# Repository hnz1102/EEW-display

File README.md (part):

<div align="center">
  <h1><code>EEW Display</code></h1>
</div>

ESP32-S3 firmware for a small earthquake-information display.  It shows recent
earthquakes and emergency earthquake warnings (緊急地震速報, EEW) from
[P2P地震情報](https://www.p2pquake.net/), draws the epicenters on a Google map,
and serves the same data (plus configuration) over Wi-Fi to a browser.  The
display is a 480×320 ILI9488 SPI TFT in landscape orientation; a MAX98357A
amplifier with an on-board speaker speaks EEWs and new earthquakes in Japanese.
Written in Rust (esp-idf-hal / esp-idf-svc).  The KiCad design of the board is in
[`hw/`](hw/) and a 3D-printable enclosure in [`STL/`](STL/) (see
[Hardware](#hardware)).

## Features

| Feature | Description |
|---------|-------------|
| Earthquake list | The 20 most recent events (8 rows visible, the list scrolls with the highlight): time (JST), magnitude, maximum intensity, depth, epicenter coordinates and tsunami flag |
| Map | Google Maps Static API tile (satellite or roadmap) filling the screen, with the recent epicenters drawn on it, sized by magnitude and coloured by intensity; Japan overview by default, or centred on the quake picked in the list.  The nearest well-known place, with distance and direction, is shown for the selected / new / EEW epicenter |
| EEW alert | On a warning the TFT switches to the map by itself, marks the forecast epicenter with a red `X` and shows magnitude, maximum forecast intensity and depth; the Web UI shows a red banner |
| 震度速報 | The JMA seismic-intensity flash (issued about 1.5 minutes after a quake of intensity 3 or more, before the epicenter is known) is announced and shown at once — maximum intensity and the areas that observed it — and replaced by the full report when that arrives |
| Voice | Chime + Japanese spoken announcement of every EEW, 震度速報 and newly received earthquake through the on-board MAX98357A amplifier and speaker; each can be switched off, and the volume set, in the Web UI (see [Spoken announcements](#spoken-announcements-japanese)) |
| Screen saver / idle clock | After a configurable idle time the backlight goes off, or a full-screen analog clock (JST) is shown; a button press or an EEW / new earthquake returns to the pages (see [Screen saver and idle clock](#screen-saver-and-idle-clock)) |
| Time sync | NTP (up to 4 servers) |
| Web UI | Browser-based configuration, earthquake list, map, audio controls |
| WPS | Wi-Fi Protected Setup (PBC mode), started at boot when no SSID is set |
| Syslog | Optional UDP syslog (RFC 5424) |
| Self-monitoring | Thread heartbeats and a software watchdog that restarts the unit when the feed or audio thread stalls or the WebSocket stays down; a `[DIAG]` status line every 10 minutes (see [Health monitoring](#health-monitoring)) |

---

## Hardware

The unit is a single 2-layer PCB, **EEW DISPLAY Rev.2** (139 × 64 mm), with the
3.5" TFT module plugged onto it, in a 3D-printed enclosure.

| Part | On the board |
|------|--------------|
| MCU | ESP32-S3-WROOM-1-N16R8 (16 MB flash, 8 MB octal PSRAM) |
| Display | **ILI9488 480×320** SPI TFT module (4-wire SPI, 18-bit colour), landscape.  The module's touch controller and SD-card slot are wired to the ESP32 but not used by the firmware |
| USB | USB-C (USB4105-GF-A): power, charging, and flashing / serial log through the ESP32-S3's native USB (5.1 kΩ CC pull-downs) |
| Battery | LiPo on a JST PH 2-pin connector, charged by an MCP73831 (500 mA); red LED = charging, green = charged.  A P-MOSFET power path runs the unit from USB when plugged in.  The supply voltage is read on GPIO11 through a 20 k / 20 k divider (see `adc_conversion_factor`) |
| Power switch | Slide switch (IS-1235-G) in front of the regulator |
| Regulator | SPX3819 LDO, 3.3 V |
| RTC | 32.768 kHz crystal on GPIO15/16 (the firmware falls back to the internal oscillator if absent) |
| Audio | MAX98357A I2S amplifier (48 kHz, 16-bit; SD_MODE high = on) driving an on-board speaker (UM1515IA).  The gain is set by the R12 / R13 option.  See [Spoken announcements](#spoken-announcements-japanese) |
| Buttons | Four 6 mm tactile switches: PAGE/BOOT (GPIO0), ZOOM-IN (GPIO38), ZOOM-OUT (GPIO39), MODE (GPIO40) |

### Board files ([`hw/`](hw/))

| File | Content |
|------|---------|
| [`schematic.pdf`](hw/schematic.pdf) | Schematic |
| `EEW-display.kicad_sch` / `.kicad_pcb` / `.kicad_pro` | KiCad project |
| `Library.pretty/` | Project footprints (ESP32-S3 module, TFT module, USB-C, slide switch, speaker, MAX98357A TQFN) |
| [`BOM.csv`](hw/BOM.csv) | Bill of materials with Digi-Key / Akizuki part numbers |
| `production/` | Fabrication output: Gerbers (`EEW-display.zip`), assembly BOM, pick-and-place (`positions.csv`), designators, IPC-D-356 netlist |

The hardware design is licensed under CC-BY-SA 4.0 (see the schematic title
block).

### Enclosure ([`STL/`](STL/))

| File | Part | Size (mm, bounding box) |
|------|------|------|
| `cover-v4.stl` | Cover | 161.8 × 86.8 × 31.5 |
| `body-v4.stl` | Body | 149.4 × 75.4 × 30.5 |
| `base-v4.stl` | Base | 158.5 × 89.2 × 44.3 |
| `button.stl` | Button cap (print four, one per tactile switch) | 9.0 × 9.0 × 5.5 |
| `eew-display.f3d` | Fusion 360 source of all parts | — |

### Pin assignment

| Function | GPIO |
|----------|------|
| TFT CS | 10 |
| TFT RST | 9 |
| TFT D/C | 46 |
| TFT SDI (MOSI) | 3 |
| TFT SCK | 8 |
| TFT BL (backlight, active high) | 18 |
| TFT SDO (MISO) | 17 — wired but not used (the panel is write-only here) |
| Battery voltage (ADC) | 11 |
| MAX98357A DIN / BCLK / LRCLK (WS) / SD_MODE | 7 / 6 / 5 / 4 |
| Buttons | 0 (PAGE/BOOT), 38 (ZOOM-IN, +), 39 (ZOOM-OUT, −), 40 (MODE, action) — all active-low with internal pull-ups |
| TFT touch: T_CLK / T_CS / T_DIN / T_DO / PEN | 47 / 48 / 45 / 41 / 42 — wired, not used |
| TFT SD card: CS / SDI / SDO / CLK | 12 / 13 / 14 / 21 — wired, not used |

The ILI9488 only accepts 18-bit colour over SPI, so the firmware keeps a
RGB565 framebuffer in PSRAM and sends the changed rectangle as 3 bytes per
pixel.  The SPI clock is 27 MHz.  If the picture is mirrored, red/blue are
swapped or the colours look negated on your module, adjust `MADCTL` / `INVERT`
(and `SPI_HZ` if there is noise) at the top of [`src/display.rs`](src/display.rs).

---

## Display Pages

The unit starts on the MAP page; a short press of BOOT cycles the pages.

| # | Page | Content |
|---|------|---------|
| 1 | EARTHQUAKE | Recent earthquakes (list + details of the highlighted one) |
| 2 | MAP | Full-screen Google map (480×266) between a one-line top bar (title, button legend, status icons, battery) and a two-column text band: the Japan overview, the quake picked in the list, or the EEW epicenter, with epicenters, scale bar and — for a selected / new / EEW quake — magnitude, intensity, depth, coordinates, nearest place and time |
| 3 | SYSTEM INFO | Network, power, memory, earthquake feed state, display and firmware version |

### Buttons

| Button | EARTHQUAKE page | MAP page | SYSTEM INFO |
|--------|-----------------|----------|-------------|
| PAGE/BOOT (GPIO0), short | next page | next page (returns the map to the Japan overview) | next page |
| PAGE/BOOT (GPIO0), ≥ 10 s | factory reset (NVS erased, `cfg.toml` defaults restored) | same | same |
| ZOOM-IN + (GPIO38) | highlight up | zoom in | zoom in |
| ZOOM-OUT − (GPIO39) | highlight down | zoom out | zoom out |
| MODE (GPIO40) | show the highlighted epicenter on the MAP | toggle satellite / roadmap | toggle satellite / roadmap |

While an EEW or a newly received earthquake is shown, BOOT (EXIT) returns to
the normal view.  Buttons auto-repeat after 400 ms.  While the display is idle
(backlight off or clock; see below) the first press only wakes it — its action
is not performed.

### Status icons

On every page, left of the battery in the title bar: a **Wi-Fi** icon — four
signal bars (green = strong, yellow = fair, orange = weak; dim with a red slash =
not connected / no IP address) — and a **WebSocket** icon, a chain link: green =
connected to the earthquake feed, orange with a red slash = down and
reconnecting, grey = the feed is switched off (`quake_enable`).  The chain is a
16×16 bitmap kept as a constant in `src/display_pages.rs` (flash, no RAM), drawn
pixel by pixel in the state colour.

### Quiet hours (new-earthquake announcements)

A daily window, in **JST**, in which ordinary new-earthquake announcements (chime
and speech) are not played — e.g. 23:00 to 07:00 so that a night-time M3 does not
wake the house.  **EEWs always sound**, whatever the window.  A window that runs
past midnight is fine; start = end means an empty window.  The screen and the
earthquake list are not affected, and until the clock has been synced by NTP the
unit does not mute (a missed announcement is worse than one at the wrong hour).

Set it under *Audio → Quiet hours* in the Web UI (applies immediately, stored in
NVS), or with `quiet_enable` / `quiet_start` / `quiet_end` in `cfg.toml`.  The
log says `quiet hours (23:00-07:00 JST): new-earthquake announcement skipped`
when a report is muted.

### Screen saver and idle clock

After `screen_timeout` seconds without a button press (`0` = never idle) the
display goes idle.  `idle_mode` chooses what idle means:

| `idle_mode` | While idle |
|-------------|------------|
| `"off"` (default) | The backlight is switched off.  Nothing is sent to the panel, and the picture is brought up to date in one go on wake-up |
| `"clock"` | A full-screen analog clock (JST) is shown instead of the pages |

Any button press, an EEW, a newly received earthquake or a system message (such
as the factory-reset countdown) ends the idle state; the button press that does
so does nothing else.  Set both under *Display* in the Web UI (applies
immediately) or in `cfg.toml`.  Spoken announcements are independent of the
screen.

The clock face fills the panel height: a metallic bezel, a gradient dial with
orange marks at 12 / 3 / 6 / 9, a cyan hour hand, a white minute hand and an
orange second hand, all lit from the top-left with soft drop shadows.  The date
is shown outside the dial — month/day and year top-left, weekday top-right
(Saturday blue, Sunday red).  Before the clock has synced (NTP) only the face is
drawn.

Rendering notes:

- The clock is drawn into an off-screen RGB888 canvas with real alpha blending,
  then converted to RGB565.  The static dial is rendered once and cached
  (~300 KB PSRAM); each second only the hands are drawn.
- The frame for the next second is rendered ahead and sent 50 ms before that
  second starts, so the second hand moves on time.  The serial log prints
  `Idle clock: frame rendered in N ms` when the clock starts.
- The date uses anti-aliased glyphs pre-rendered from DejaVu Sans Condensed Bold
  (`src/clock_font_data.rs`, ~27 KB), since the bitmap fonts look stair-stepped
  when enlarged.  Regenerate them with
  `python3 tools/clock_font/gen_clock_font.py [font.ttf]` (needs Pillow).

### TFT screenshots

Rendered by [`tools/screenshots`](tools/screenshots) from the firmware's own
drawing code.  **The earthquake data is synthetic sample data (made-up events,
not live)** — the pages that show it carry a caption saying so.  The map is a
real Google Maps tile when the tool is given a key (see below), else a schematic
stand-in.

| | | |
|---|---|---|
| <br>**EARTHQUAKE** | <br>**MAP** (overview) | <br>**MAP** (quake picked from the list) |
| <br>**MAP** (new earthquake) | <br>**MAP** (EEW) | <br>**SYSTEM INFO** |
| <br>**EARTHQUAKE** (waiting for data) | <br>System message overlay | <br>**MAP** (satellite) |
| <br>Idle clock (`idle_mode = "clock"`) | | |

---

## Earthquakes and EEW (P2P地震情報)

With `quake_enable = "true"` in `cfg.toml` (the default) the unit shows recent
earthquakes and emergency earthquake warnings (緊急地震速報, EEW) from
[P2P地震情報](https://www.p2pquake.net/) (JSON API v2).  The data is
originally issued by the Japan Meteorological Agency (気象庁).  It needs Wi-Fi
and a synced clock (NTP), because the connection is TLS.

| Where | What you get |
|-------|--------------|
| **EARTHQUAKE** page (TFT) | The 20 most recent events (8 rows visible, the list scrolls with the highlight): time (JST), magnitude, maximum intensity (`I5-` = 5弱, `I5+` = 5強, …), depth and epicenter coordinates; tsunami warnings are flagged.  **+ / −** move the highlight, the **action** button (GPIO40) shows the highlighted epicenter on the MAP page |
| **MAP** page | Epicenters of recent earthquakes inside the visible map are drawn as circles — sized by magnitude, coloured by maximum intensity — with a label such as `M5.2 I5-` |
| **Web UI** (configuration page) | A *Recent Earthquakes* card with the epicenter name (Japanese), magnitude, intensity, depth and tsunami status.  The epicenter name opens the Web UI map (`/map?lat=…&lon=…&zoom=…`) centred on it |
| **震度速報** | An orange band on the MAP page (`SHINDO REPORT Imax 3`, `Epicenter: pending`, number of areas at the maximum intensity, quake time), the title `SHINDO 3 (no epicenter yet)`, a status line on the EARTHQUAKE page, and an orange banner in the Web UI with the area names in Japanese.  It disappears when the epicenter report for the same quake arrives, or after 15 minutes |
| **EEW alert** | On a warning the TFT switches to the MAP page by itself and centres the forecast epicenter: a large red `X`, the header turns red (`!! EEW M6.3 I5- !!`) and a box at the bottom right of the map shows magnitude, maximum forecast intensity, depth, coordinates and issue time.  The Web UI shows a red banner with the forecast areas |

The TFT font is ASCII only, so Japanese epicenter and area names appear in the
Web UI only; the TFT shows the coordinates and, on the MAP page, the nearest
well-known place with distance and direction (e.g. `45km ESE of Iwaki`, from a
built-in table of ~75 cities and islands in [`src/place.rs`](src/place.rs), so it
works offline and for epicenters at sea).  The unit has no position sensor, so
it does not compute the distance to the epicenter.

How it works (`src/quake.rs`):

- A WebSocket (`wss://api.p2pquake.net/v2/ws`) receives the events as they are
  registered.  Warnings (code 556) raise the alert, earthquake reports (551) are
  merged into the list.  A 551 report comes in up to three steps: 震度速報
  (`ScalePrompt`, intensities only, ~1.5 min after the quake), 震源情報
  (`Destination`, epicenter and magnitude) and 各地の震度 (`DetailScale`).  The
  first is announced as a 震度速報 (ignored if older than 20 minutes or the quake
  is already in the list); the later ones complete the list entry and trigger
  the new-earthquake announcement.  Note that P2P地震情報 relays EEWs (556) only
  at warning level (警報), not forecasts (予報).
- Messages are reassembled from the WebSocket frames by offset (up to 256 KB —
  a `DetailScale` report can be ~80 KB), so a chunk boundary inside a UTF-8
  character does not lose the message.  Every 551 / 552 / 556 message is logged
  on arrival as `[WS] rx code 551 type Destination 591 B`.  Test messages and warnings older than 3 minutes (by
  their issue time) are ignored, so a boot in the middle of an old event does
  not alert.
- REST (`/v2/history`) loads the initial list (the 20 latest events) at boot,
  re-syncs it every 30 minutes, and takes over — polling every 10 s (EEW) /
  60 s (list) — while the WebSocket is down.
- The WebSocket pings every 30 s and reconnects by itself 30 s after a drop
  (the server also closes long-lived connections now and then, e.g. after about
  an hour); it is only recreated after it has stayed down for 180 s.  If it
  cannot be opened because internal RAM is short, the REST client is released
  first; if it stays down for 30 minutes the unit restarts (see
  [Health monitoring](#health-monitoring)).
- Network use waits for an IP address: the map and the feed start as soon as
  Wi-Fi reports one (tracked from system events, not by polling the driver).
- **Memory:** the TLS WebSocket holds roughly 30 KB of internal RAM, which
  competes with the map tile download.  The WebSocket is therefore dropped for
  the duration of every map fetch and re-created once the map has been idle for
  about 12 s; any warning issued in the gap is recovered by a REST check right
  after it reconnects.  REST polling is skipped while internal RAM is low or a
  map fetch is running.  Watch *Free Heap (Internal)* in the Web UI and
  `[HEAP]` / `[WS]` / `[QUAKE]` in the log.
- The WebSocket needs the `esp_websocket_client` ESP-IDF component, pulled from
  the component registry at build time (declared in `Cargo.toml`), so the first
  build needs network access.

**Testing without a real earthquake.**  Build with the sandbox feature:

```bash
cargo build --release --features quake-sandbox
```

This points the feed at the P2P sandbox, which replays old data (including a
2023 Hokkaido EEW) and skips the "older than 3 minutes" check, so the whole
alert path fires right after boot.  Never ship a sandbox build.

> **Not a safety device.**  Delivery is not guaranteed and can be delayed; the
> warning only covers what the Meteorological Agency issues as a warning.  Do
> not rely on this unit for life-safety decisions.  Use the official channels.
> Use of the data is subject to the P2P地震情報
> [terms for secondary use](https://www.p2pquake.net/secondary_use/): credit the
> Japan Meteorological Agency and P2P地震情報 (the Web UI card already does).

### Health monitoring

[`src/health.rs`](src/health.rs) watches the threads that the screen does not
show.  The earthquake-feed thread and the audio thread record a heartbeat with
their current stage every time round their loops; the main loop checks them.

| Condition | Action |
|-----------|--------|
| Feed thread has not moved for 180 s | Log `[WDOG] quake thread stuck … at <stage>` and restart |
| Audio thread has not moved for 60 s | Log `[WDOG] audio thread stuck … at <stage>` and restart |
| WebSocket not connected for 30 minutes (not while speaking or during an EEW) | Log `[WDOG] …` and restart |

The reason is kept in RTC memory, which survives the restart, and logged again
after the next boot as `[WDOG] previous run was restarted by the watchdog: …`, in
case the line before the restart did not reach syslog.  Every 10 minutes a line
like

```
[DIAG] quake: 3 s ago at sleep | audio: 0 s ago at recv playing=false | ws=true rx 42 msgs, last 312 s ago map_busy=false | internal 61234 B (min 40120) psram 7012 KB
```

shows each thread's stage, the WebSocket state and how many messages it has
received, and the internal RAM / PSRAM headroom.

---

## Spoken announcements (Japanese)

With `audio_enable = "true"` the unit speaks through the on-board MAX98357A and
speaker:

- **EEW**: a 1.5 s arpeggio chime (seven notes with harmonics, about 20
  frequency components; the pitch steps up at 0.4 s), then
  「緊急地震速報。震源は福島県沖です。マグニチュード6点1。最大震度6弱と予測されます。強い揺れに警戒してください。」
  The chime + sentence is played twice (`EEW_REPEATS` in `src/voice.rs`).  Played
  for the first report of an event, and for later reports only when the forecast
  maximum intensity rises.  It interrupts anything else.
- **New earthquake** (pushed over the WebSocket, not the list loaded at boot): a
  "ピンポン" chime, then the sentence once:
  「地震情報。震源は茨城県南部です。マグニチュード4点6。最大震度4。深さ50キロ。この地震による津波の心配はありません。」
  Dropped if an EEW is being spoken, and during the [quiet hours](#quiet-hours-new-earthquake-announcements) if set (EEWs ignore those).
- **震度速報** (intensity flash, before the epicenter is known): the "ピンポン"
  chime, then
  「震度速報。最大震度3。最大震度を観測した地域は、福島県中通り、福島県浜通り、茨城県北部、栃木県南部などです。」
  Up to four areas that observed the maximum intensity are named (「など」 when
  there are more); an area whose name cannot be spoken in full is left out
  rather than cut short.  Spoken again only if a later flash raises the maximum
  intensity.  Follows the new-earthquake switch and the quiet hours.

The chimes are generated by the firmware — sustained / bell-like notes with a
reverb that is applied to the chime only, not to the speech — so they also sound
without a voice bank.  The audio thread runs at a raised priority on core 1 with a
~60 ms I2S DMA buffer, so that the TLS / JPEG work of a simultaneous map refetch
cannot make the sound break up.
The speech is **not synthesized on the device and needs no network or API key at
run time**.  It is generated once on a PC with Google Cloud Text-to-Speech as
~360 short parts (fixed phrases, numbers 0–99 and 100–700, the nine seismic
intensities, and parts of region names such as 福島県 + 沖) and flashed to a
dedicated `voice` partition; the firmware strings the parts together.  A
hypocenter name is spoken as far as its parts match (so 福島県沖 = 福島県 + 沖); a
name with an unknown part is cut short instead of being misread.  To cover more
names, add parts to [`tools/voice/tokens.txt`](tools/voice/tokens.txt) and
regenerate.  All 181 JMA intensity-report area names seen in the P2P history
(e.g. 福島県中通り, 東京都２３区, 熊本県熊本) can be spoken in full.

> v0.4.0 added parts for the 震度速報 sentence.  After updating from an older
> version, regenerate and re-flash `voice.bin` as well (`./flash.sh` or
> `./flash.sh --voice-only`), or the announcement is incomplete.

### 1. Generate `voice.bin` (once, on a PC)

Enable the **Cloud Text-to-Speech API** in the Google Cloud project (and allow it
on the API key if the key has API restrictions), then:

```bash
cd tools/voice
GOOGLE_TTS_API_KEY=your-key python3 gen_voice.py            # default voice ja-JP-Neural2-B
# python3 gen_voice.py --voice ja-JP-Neural2-C --rate 1.05   # other voice / speed
```

Each part is synthesized once and cached in `tools/voice/cache/`, so re-running
costs no API calls unless a part changed (~340 short requests, within the free
tier).  `python3 gen_voice.py --dry-run` makes a `voice.bin` of tone bursts with
no API call — only to test the flashing and playback path.  Check the Google
Cloud TTS terms and pricing for your use; the generated audio is yours to flash
into your own device.

### 2. Flash

The `voice` partition (9 MB at `0x700000`) is part of `partitions.csv`, so the
firmware has to be flashed once to write the new partition table, then the voice
bank.  [`flash.sh`](flash.sh) does both, then opens the monitor:

```bash
./flash.sh                  # firmware + partition table, voice bank, monitor
./flash.sh --voice-only     # only the voice bank (after regenerating voice.bin)
./flash.sh --no-voice       # firmware only
./flash.sh --port /dev/ttyACM1 --no-monitor
```

By hand: `cargo espflash flash --release`, then
`cargo espflash write-bin 0x700000 tools/voice/voice.bin`.

A hand-built merged image (`cargo espflash save-image --merge complete_flash.bin`)
does not contain the voice bank; flash `voice.bin` separately as above.
`build-flash-images.sh`, however, folds `voice.bin` into its output when it is
present (see [Build](#creating-a-complete-flash-binary-image)), so that one file
carries it.  The boot log shows `[VOICE] bank loaded: N parts` (or why
announcements are off).

### 3. Test

The Web UI configuration page has an **Audio** card (shown when `audio_enable =
"true"`): *Test EEW voice*, *Test new-quake voice* and *Test 震度速報 voice* play sample announcements
(also when the matching switch is off), and the sine test tone (100 Hz – 15 kHz,
off by default) can be switched on and tuned.  The same card has the **volume**
slider (applied while you drag, stored in NVS on release) and the **Announce**
switches: EEW and new-earthquake announcements (chime + speech) can each be
turned on or off (both on by default; stored in NVS and overriding
`voice_eew` / `voice_new` in `cfg.toml`).

---

## Architecture

```
p2pquake.net ◄── quake.rs (WebSocket: EEW + events, REST fallback)
                    │
                    ├── display.rs ── ILI9488 driver + RGB565 framebuffer, screen saver / idle clock
                    │      └── display_pages.rs (EARTHQUAKE / MAP / SYSTEM INFO / clock drawing)
                    │             └── place.rs (epicenter → nearest place text)
                    ├── map_display.rs ── persistent fetch worker ──► Google Static Maps (HTTPS)
                    ├── voice.rs ── sentences from the `voice` flash partition
                    │      └── audio.rs ── I2S → MAX98357A (chimes, ADPCM speech, test tone)
                    └── httpserver.rs ── Web UI: config, quake list, map, audio
btn_ctrl.rs (buttons) · wifi.rs (STA, WPS, reconnect, network state) · boot_log.rs
```

---

## Directory Layout

```
eew-display/
├── src/
│   ├── main.rs           # Entry point, peripheral initialisation
│   ├── display.rs        # ILI9488 SPI driver, framebuffer, display task, screen saver / idle clock
│   ├── display_pages.rs  # Page drawing (earthquake, map, info, idle clock); no ESP-IDF dependency
│   ├── clock_font_data.rs # Generated anti-aliased glyphs for the idle clock's date
│   ├── map_display.rs    # Map tile fetch, JPEG decode, zoom
│   ├── audio.rs          # MAX98357A I2S output: voice playback (ADPCM) + test tone
│   ├── voice.rs          # Spoken-announcement sentences from the `voice` partition
│   ├── place.rs          # Epicenter → nearest place text (offline table)
│   ├── quake.rs          # Earthquake list + EEW (P2P地震情報 WebSocket / REST)
│   ├── httpserver.rs     # HTTP server, NVS config management
│   ├── wifi.rs           # Wi-Fi STA connection (DHCP / static IP), WPS, reconnect, event-driven network state
│   ├── health.rs         # Thread heartbeats, watchdog restart, [DIAG] status line
│   ├── syslogger.rs      # UDP Syslog logger (RFC 5424)
│   ├── btn_ctrl.rs       # Button handling
│   └── boot_log.rs       # NVS boot counter and rolling reset-reason log (last 10 entries)
├── tools/
│   ├── voice/            # PC tool: generates voice.bin (Google Cloud TTS) — see Spoken announcements
│   ├── screenshots/      # Host tool: renders every TFT page to PNG (see below)
│   ├── clock_font/       # PC tool: generates src/clock_font_data.rs from a TTF
│   └── webui_screenshots/ # Host tool: screenshots of the Web UI pages (see Web UI)
├── docs/images/          # README images; tft/ = TFT screenshots, webui/ = Web UI screenshots
├── hw/                   # KiCad schematic / PCB, BOM and fabrication files (see Hardware)
├── STL/                  # 3D-printable enclosure (STL) + Fusion 360 source
├── cfg.toml              # Build-time default configuration (gitignored — contains credentials)
├── cfg.toml.tmp          # Template for cfg.toml (safe to commit)
├── espflash.toml         # espflash settings (16 MB flash, partition table)
├── sdkconfig.defaults    # ESP-IDF build settings
├── partitions.csv        # Flash partition table
├── flash.sh              # Flash firmware + partition table + voice bank, then monitor
├── setup_env.sh          # One-shot environment setup (Rust, espup, udev)
└── build-flash-images.sh # Build a merged flash image from the cfg.toml.tmp defaults
```

---

## Configuration

### cfg.toml (build-time defaults)

`cfg.toml.tmp` is the only template.  Before building, copy it to `cfg.toml`
(which is not committed, since it holds your Wi-Fi credentials and API key):

```bash
cp cfg.toml.tmp cfg.toml
```

Then edit `cfg.toml` for your environment.  The table name must match the crate
name, `[eew-display]`, or the values are ignored.

Every key is optional; a missing key uses the built-in default below.  The
shipped `cfg.toml.tmp` template already sets `screen_timeout = "300"` and
`audio_enable = "true"`.

| Setting | Built-in default | Change it when |
|---------|---------|----------------|
| `display_enable` | `"true"` | There is no TFT |
| `screen_timeout` | `"0"` | You want the display to go idle after N seconds without a button press (`0` = never); also in the Web UI |
| `idle_mode` | `"off"` | What idle shows: `"off"` = backlight off, `"clock"` = analog clock; also in the Web UI |
| `quake_enable` | `"true"` | You want to turn the earthquake / EEW feed off.  The feed keeps a TLS WebSocket open (~30 KB of internal RAM) and needs Wi-Fi plus a synced clock.  Read at boot only, so rebuild after changing it |
| `audio_enable` | `"false"` (template: `"true"`) | `"true"` starts the audio output (voice announcements + Web UI test tone); set `"false"` to keep the amplifier off |
| `audio_volume` / `voice_eew` / `voice_new` | `"70"` / `"true"` / `"true"` | Voice volume in percent, and whether EEWs / new earthquakes are announced.  The Web UI overrides these (stored in NVS) |
| `quiet_enable` / `quiet_start` / `quiet_end` | `"false"` / `"23:00"` / `"07:00"` | Mute new-earthquake announcements (not EEW) between the two times of day, JST; see [Quiet hours](#quiet-hours-new-earthquake-announcements) |
| `adc_conversion_factor` | `"80.098"` (template: `"437.98"`) | The battery voltage divider differs: voltage = raw ADC reading ÷ this factor |
| `web_user` / `web_password` | `admin` / `esp32` | Always — these protect the Web UI |
| `maps_api_key` | empty | You want the map (see [Google Maps API key](#google-maps-api-key)) |

```toml
[eew-display]
wps_enable     = "true"     # "true": use WPS PBC on next boot when SSID is empty
wifi_ssid      = ""         # your-ssid
wifi_psk       = ""         # your-password
ip_mode        = "dhcp"           # "dhcp" or "static"
ip_address     = "192.168.0.200"
subnet_mask    = "255.255.255.0"
gateway        = "192.168.0.1"
dns            = "1.1.1.1"

syslog_server    = "192.168.0.140:514"
syslog_enable    = "false"
syslog_host_name = "esp32s3"
syslog_app_name  = "eew-display"

web_user     = "admin"
web_password = "esp32"

display_enable = "true"
idle_mode = "off"          # what to show when idle: "off" (backlight off) or "clock" (analog clock)
screen_timeout = "300"     # backlight off after this many idle seconds (0 = always on)

ntp_server1 = "time.aws.com"
ntp_server2 = "time.google.com"
ntp_server3 = "time.cloudflare.com"
ntp_server4 = "ntp.nict.jp"

adc_conversion_factor = "437.98"

quake_enable         = "true"

audio_enable         = "true"    # MAX98357A: voice announcements + Web UI test tone
audio_volume         = "70"      # voice volume, percent (0-100)
voice_eew            = "true"    # announce EEWs (chime + speech)
voice_new            = "true"    # announce new earthquakes (chime + speech)
quiet_enable         = "false"   # "true": no NEW-earthquake announcements between quiet_start and quiet_end (JST)
quiet_start          = "23:00"
quiet_end            = "07:00"

maps_api_key = ""
```

Values in `cfg.toml` are compiled into the firmware as defaults.
After boot they can be overridden via the Web UI or direct NVS writes; NVS values take priority.
A factory reset (hold BOOT ≥ 10 s, or *Reset Defaults* in the Web UI) erases NVS and
returns to the `cfg.toml` values.

The Web UI configuration page has these cards: *Device Status*, *Recent
Earthquakes*, *Audio*, *WiFi* (SSID, password, WPS), *Network* (DHCP / static
IP), *Syslog*, *Authentication*, *Display* (screen timeout), *NTP Servers* and
*Map Settings* (map type, Maps API key), plus *Boot Log*, *Reboot* and *Reset
Defaults*.

### Google Maps API key

The map pages (LCD and Web UI) download images from the **Maps Static API**, so
they need a Google Maps Platform API key.  Without `maps_api_key` the MAP page
has nothing to draw the epicenters on (there is no local tile cache), although
the EARTHQUAKE list and EEW alerts keep working.

**Where to get one**

1. Sign in to the [Google Cloud console](https://console.cloud.google.com/) and
   create (or select) a project.
2. Link a **billing account** to the project.  Maps Platform APIs require one,
   even though usage within the free monthly allowance is not charged — see the
   [Google Maps Platform pricing](https://mapsplatform.google.com/pricing/) page
   for the current allowance.
3. Open **APIs & Services → Library**, search for **Maps Static API** and click
   **Enable**.
4. Open **APIs & Services → Credentials**, click **Create credentials → API key**
   and copy the key.  Step-by-step instructions are in Google's
   [Maps Static API documentation](https://developers.google.com/maps/documentation/maps-static/get-api-key).
5. Enter the key in the Web UI: **Config page → Map Settings → Google Maps API
   Key**, then **Save**.  It takes effect immediately (no reboot) and is stored
   in NVS.  To have a key built in as the default instead (for a fresh or
   factory-reset device), set it in `cfg.toml` and rebuild:

   ```toml
   maps_api_key = "your-api-key"
   ```

**Notes**

- The key is stored in NVS and can be changed from the Web UI at any time.
  `maps_api_key` in `cfg.toml` is only the default, used until a key is saved
  and restored by a factory reset (saving an empty field also falls back to it).
- The Web UI map pages load images directly from Google in your browser, so the
  device hands the key to any logged-in browser (`/api/mapkey`).  Keep the
  device login password strong, and do not share firmware images built with your
  own key (`build-flash-images.sh` builds from `cfg.toml.tmp`, whose key is empty).
- In the Cloud console, restrict the key under **API restrictions** to the
  **Maps Static API** only, and set a budget alert or quota so a leaked key cannot
  run up a bill.  An application restriction (HTTP referrer / IP) is awkward here
  because requests come both from the device and from browsers on your LAN.
- `cfg.toml` is not committed.  Never put a real key in `cfg.toml.tmp`, which is
  the template that gets committed.  Because the Web UI can set the key, you can
  leave `cfg.toml` empty and keep the key out of the build entirely.

---

## Wi-Fi Setup with WPS

**WPS (Wi-Fi Protected Setup)** allows you to connect to a Wi-Fi network without manually entering the SSID and password. This device supports **WPS Push Button Configuration (PBC)** mode.

WPS runs **at boot, when `wps_enable = "true"` and no SSID is stored**; there is no
"Start WPS" button in the Web UI (the *WiFi* card only has the *WPS* Enable /
Disable switch and the SSID / password fields).

### Method 1: Using cfg.toml (initial setup)

1. **Edit `cfg.toml` before building**:
   ```toml
   wifi_ssid      = ""           # empty: no credentials
   wps_enable     = "true"       # use WPS when there is no SSID
   ```
2. **Flash the firmware** to the device.
3. On boot the screen shows *WPS MODE*: **press the WPS button on your Wi-Fi
   router within 120 seconds**.
4. On success the credentials are saved to NVS and the unit carries on connecting
   (no reboot needed).  They persist across reboots.

### Method 2: Switch an already configured unit to WPS

- Perform a **factory reset** (hold the BOOT button, GPIO0, for **≥ 10 s**): NVS is
  erased, the `cfg.toml` defaults are restored (so an empty `wifi_ssid` with
  `wps_enable = "true"` in `cfg.toml` gives WPS again) and the unit reboots.
- Or, in the Web UI, clear the SSID, set *WPS* to *Enable*, **Save** and reboot.

### If WPS fails

If no WPS handshake succeeds within 120 s the unit stays **without Wi-Fi until the
next boot** (and therefore without the Web UI, the map and the earthquake feed).
Reboot to try again, or enter the credentials in `cfg.toml` / the Web UI.

### Wi-Fi reconnection

A background monitor checks every 30 s (after a 15 s grace period) and calls
`esp_wifi_connect()` when the station is not associated; after three failures in a
row it also restarts the Wi-Fi driver.  The router being unreachable makes the
driver log `Haven't to connect to a suitable AP now!` — that is the driver
retrying, not an error of this firmware.

### Notes

- WPS PBC mode is the only supported WPS method (PIN mode is not supported).
- You can always set the credentials in `cfg.toml` or the Web UI instead.

---

## Environment Setup

Run `setup_env.sh` **once** on a fresh Ubuntu / Debian machine (or WSL2) before
building.  The script performs all steps below automatically.

```bash
bash setup_env.sh
```

After the script finishes, open a new terminal (or reload your shell config) so
the environment variables take effect:

```bash
source "$HOME/.cargo/env"
source ~/export-esp.sh
```

### What the script does

| Step | Action |
|------|--------|
| 1 | Install system packages via `apt` |
| 2 | Install Rust toolchain via `rustup` (skipped if already present) |
| 3 | Install `ldproxy`, `espup`, `cargo-espflash` via Cargo |
| 4 | Install & update the ESP32-S3 Xtensa toolchain via `espup` |
| 5 | Source `~/export-esp.sh` (generated by `espup`) |
| 6 | Add udev rule for ESP32 USB device (`303a:1001`) and reload rules |

> If you prefer to run the steps manually, expand the section below.

<details>
<summary>Manual setup steps</summary>

```bash
# 1. System packages
sudo apt update && sudo apt -y install \
    git python3 python3-pip gcc build-essential curl \
    pkg-config libudev-dev libtinfo5 clang libclang-dev \
    llvm-dev udev libssl-dev python3.10-venv

# 2. Rust
curl --proto '=https' --tlsv1.2 -sSf https://sh.rustup.rs | sh
# Select option 1 (default install), then:
source "$HOME/.cargo/env"

# 3. Cargo tools
cargo install ldproxy
cargo install espup
cargo install cargo-espflash

# 4. ESP32-S3 toolchain
espup install
espup update

# 5. Activate ESP environment (add to ~/.bashrc / ~/.zshrc for persistence)
. ~/export-esp.sh

# 6. udev rules
sudo sh -c 'echo "SUBSYSTEMS==\"usb\", ATTRS{idVendor}==\"303a\", ATTRS{idProduct}==\"1001\", MODE=\"0666\"" > /etc/udev/rules.d/99-esp32.rules'
sudo udevadm control --reload-rules
sudo udevadm trigger
```

</details>

---

## Build and Flash

### Prerequisites

- Rust toolchain: `esp` channel (selected automatically via `rust-toolchain.toml`)
- [espup](https://github.com/esp-rs/espup) — ESP32-S3 Xtensa toolchain
- [espflash](https://github.com/esp-rs/espflash)
- ESP-IDF v5.4.2 (fetched automatically by the build)
- Python 3 (standard library only) for `tools/voice/gen_voice.py`

### Build

```bash
cp cfg.toml.tmp cfg.toml    # then edit it
cargo build --release
```

The first build downloads the `esp_websocket_client` component (used by the
[earthquake feed](#earthquakes-and-eew-p2p地震情報)), so it needs network access.
Add `--features quake-sandbox` to test that feed against the P2P sandbox.

### Flash and monitor

```bash
./flash.sh                              # firmware + partition table + voice bank, then the monitor
cargo espflash flash --release --monitor   # firmware + partition table only
```

[`flash.sh`](flash.sh) also writes `tools/voice/voice.bin` to the `voice`
partition (see [Spoken announcements](#2-flash)).  The first flash after
pulling the voice feature must include the partition table, as both commands do.

### Creating a complete flash binary image

To create a single binary file with the bootloader, partition table and application (no voice bank) for distribution or web-based flashing:

```bash
cargo espflash save-image --release --merge --chip esp32s3 complete_flash.bin
```

To build a merged image from the `cfg.toml.tmp` defaults in one go (Wi-Fi and
API key unset, for distribution), run `build-flash-images.sh`.  The 16 MB image
is written to `flash_images/flash_eew-display.bin`; flash it alone to **0x0**.
When `tools/voice/voice.bin` exists it is folded into the image at the `voice`
partition offset (0x700000), so the one file also carries the spoken
announcements — otherwise the image is built without them and the script says so.
Your own `cfg.toml` is restored afterwards.

**Important**: When flashing a merged image, always write it to **offset 0x0**, not 0x9000. Writing to 0x9000 will result in a boot failure with "invalid header: 0xffffffff" error.

#### Flash the complete binary

```bash
# Using esptool.py
esptool.py --chip esp32s3 --port /dev/ttyACM0 write_flash 0x0 complete_flash.bin

# Using espflash
espflash write-bin 0x0 complete_flash.bin
```

#### Web-based flashing (no command line required)

You can also flash the binary via a web browser using the ESP Web Flasher:

1. Open [https://thelastoutpostworkshop.github.io/ESPConnect/](https://thelastoutpostworkshop.github.io/ESPConnect/) in Chrome, Edge, or Opera (Web Serial API required)
2. Click **"Connect"** and select your ESP32-S3 device from the serial port list
3. Click **"Choose File"** and select `complete_flash.bin`
4. Set the flash address to **`0x0`** (very important!)
5. Click **"Program"** to start flashing
6. Wait for the process to complete and click **"Reset Device"**

### Flash layout

| Partition     | Offset   | Size                |
|---------------|----------|---------------------|
| nvs           | 0x9000   | 24 KB               |
| phy_init      | 0xF000   | 4 KB                |
| factory (app) | 0x10000  | 0x6F0000 (7104 KB)  |
| voice (data)  | 0x700000 | 0x900000 (9 MB)     |

Flash: 16 MB, DIO mode, 40 MHz.  The `voice` partition holds `tools/voice/voice.bin`
(~2.4 MB); see [Spoken announcements](#spoken-announcements-japanese).

### Regenerating the TFT screenshots

`tools/screenshots` is a small host-side crate (separate from the firmware, built
with the stable toolchain for your PC) that compiles the firmware's own
`src/display_pages.rs` and renders each page into a 480×320 framebuffer, then
writes PNGs.  Quake and map data are replaced by stubs filled with sample data
(pages that show it get a "sample data" caption band under the image).

```bash
cd tools/screenshots
cargo run --release -- [OUT_DIR] [SCALE]    # default: ../../docs/images/tft, 1
```

Map pages fetch real tiles with the same Static Maps request the firmware uses.
The key is taken from the `GOOGLE_MAPS_API_KEY` environment variable, else
`maps_api_key` in `cfg.toml`; tiles are cached in `tools/screenshots/.tile-cache/`
(gitignored).  Without a key — or with `SCREENSHOTS_OFFLINE=1` — a schematic map
is drawn instead.  The firmware version on the SYSTEM INFO sample is read from
`Cargo.toml`.

---

## Web UI

Once the device is on Wi-Fi it serves a Web UI at `http://<device_ip>/` (port 80).
Sign in with `web_user` / `web_password` (default `admin` / `esp32` — change
them).  The screenshots below were rendered from the firmware's own page HTML
against a mock of the device API with **synthetic sample data** (made-up
earthquakes and network); see [Regenerating the Web UI screenshots](#regenerating-the-web-ui-screenshots).

### Sign in

### Configuration page

The page has a card per topic.  *Save to NVS* stores the settings (most apply
immediately; *Reboot* applies the rest), *Reset Defaults* erases NVS and returns to
the `cfg.toml` values, and *Boot Log* shows the reset reasons of the last boots.

| Card | What it does |
|------|--------------|
| **Device Status** | Firmware version and build date, IP address, SSID, signal strength, battery voltage, chip temperature, free internal RAM and PSRAM (refreshed every 3 s) |
| **Recent Earthquakes** | The latest events with the epicenter name in Japanese (a link to the Web UI map centred on it), magnitude, intensity, depth and tsunami status; a red banner while an EEW is active, an orange one for a 震度速報 |
| **Audio** | Test tone on/off with a 100 Hz – 15 kHz slider, **Volume** slider, **Announce** switches for EEW / new earthquake, **Quiet hours** (a daily window with no new-earthquake announcements; EEW always sounds), and *Test EEW voice* / *Test new-quake voice* / *Test 震度速報 voice* buttons (shown when `audio_enable = "true"`) |
| **WiFi / Network** | SSID and password, WPS enable, DHCP or static IP |
| **Syslog** | Optional remote logging (server, host name, app name) |
| **Authentication** | The Web UI user name and password |
| **Display** | Idle timeout (seconds) and what to do when idle: switch the backlight off, or show the analog clock |
| **NTP Servers** | Up to four time servers |
| **Map Settings** | Map type (satellite / roadmap) and the Google Maps API key |

While an EEW is active the *Recent Earthquakes* card shows the warning at the top,
with a link that opens the map framed on the forecast epicenter:

### Map page

`/map` shows the recent epicenters on a Google map, drawn in the browser: circles
sized by magnitude and coloured by maximum intensity, labelled like `M5.4 I5弱`.
−/+ change the zoom and the satellite / road button switches the map type (both
act on the device's own map too).  `/map?lat=…&lon=…&zoom=…` views an arbitrary
point — the earthquake list links to it — and *Overview* returns to the Japan
view.

| Overview | Epicenter view | During an EEW |
|---|---|---|
|  |  |  |

The map page downloads its images directly from Google using the Maps API key the
device hands to a signed-in browser (see [Google Maps API key](#google-maps-api-key)).

### Regenerating the Web UI screenshots

[`tools/webui_screenshots/capture.py`](tools/webui_screenshots/capture.py) pulls the
login, configuration and map pages out of `src/httpserver.rs`, fills the
configuration template with sample settings, serves them from a small local mock of
the device API, and photographs them with headless Firefox:

```bash
python3 tools/webui_screenshots/capture.py      # writes docs/images/webui/
```

It needs Firefox and Pillow.  Each distinct map view is fetched **once** from
Google with the key from `GOOGLE_MAPS_API_KEY` (else `maps_api_key` in `cfg.toml`)
and cached in `tools/webui_screenshots/.tile-cache/` (gitignored), so re-running
costs no API calls; without a key a grey placeholder is used.  The key never
appears in the pictures.  (A snap-packaged Firefox can only write below your home
directory, so keep the output folder there.)

---

## Web UI Endpoints

Once the device is on Wi-Fi, the Web UI is at `http://<device_ip>/` (login
required: `web_user` / `web_password`).

| URL | Method | Description |
|-----|--------|-------------|
| `/login` | GET / POST | Login |
| `/logout` | GET | Logout |
| `/` | GET | Configuration page, device status and recent earthquakes (auth required) |
| `/map` | GET | Map page with the recent epicenters; `?lat=&lon=&zoom=` views an arbitrary point (e.g. an epicenter) |
| `/api/mapinfo` | GET | Map centre and zoom the TFT is showing (JSON) |
| `/api/quakes` | GET | Recent earthquakes, the active EEW and the pending 震度速報 (`prompt`: time, intensity, areas, n_areas), if any (JSON; `enabled:false` when `quake_enable` is off) |
| `/api/map/pixels` | GET | Current map image (raw RGB565) |
| `/api/mapkey` | GET | Maps API key and map type, for the browser-side map |
| `/api/map/zoomin`, `/api/map/zoomout` | POST | Change map zoom |
| `/api/map/toggletype` | POST | Toggle satellite / roadmap |
| `/api/config` | POST | Save configuration to NVS |
| `/api/status` | GET | Device / Wi-Fi status, heap, firmware version and build date (JSON) |
| `/api/reset` | POST | Erase NVS and restore cfg.toml defaults |
| `/api/reboot` | POST | Reboot the device |
| `/api/boot_log` | GET | Boot history with reset reasons from NVS (JSON) |
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
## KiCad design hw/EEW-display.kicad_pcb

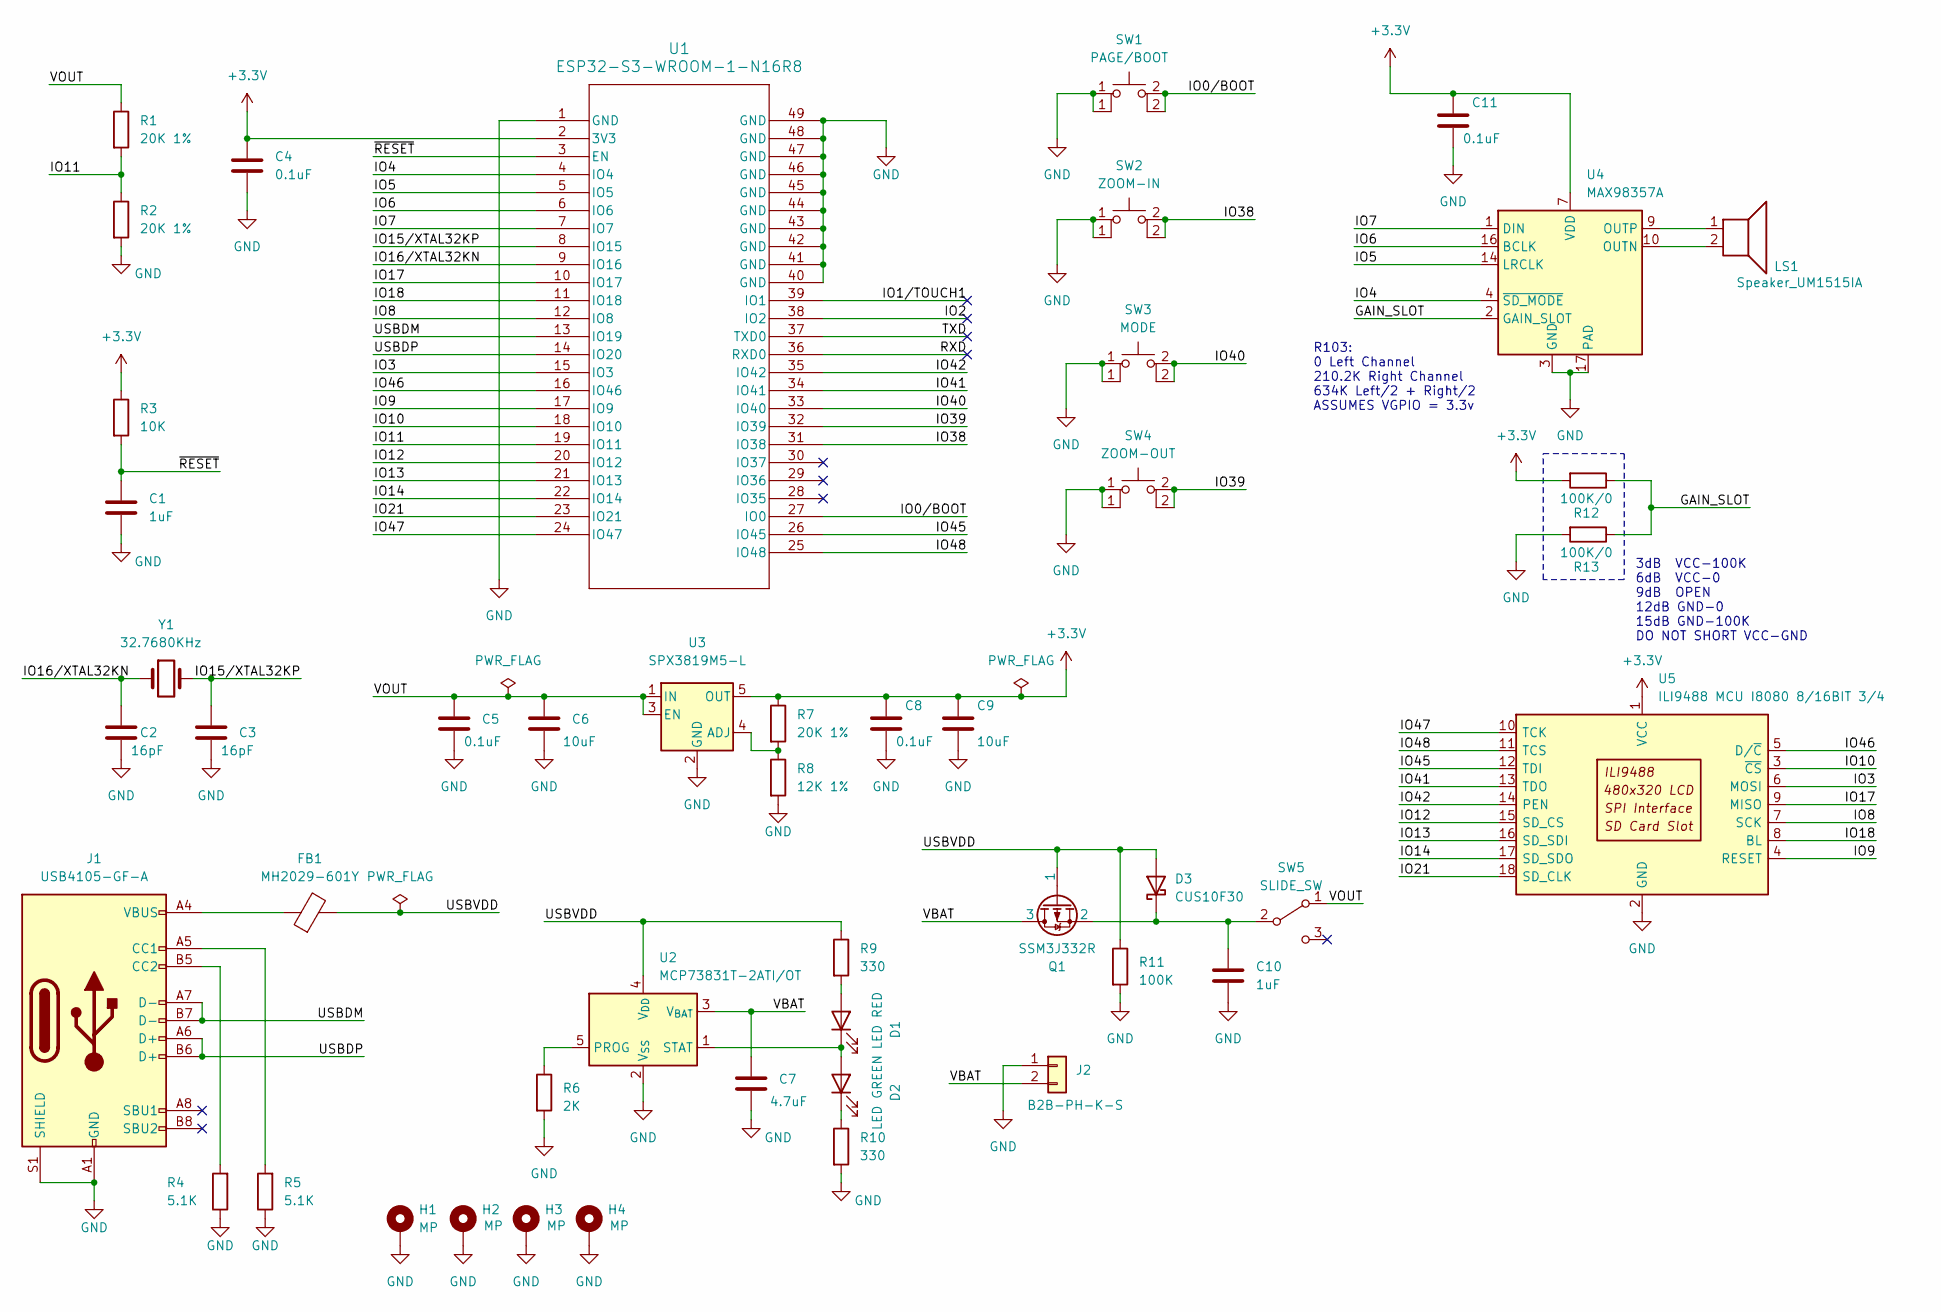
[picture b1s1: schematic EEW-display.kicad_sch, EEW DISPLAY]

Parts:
C1, C10: 1uF; C_0805_2012Metric; digikey 1276-1026-1-ND
C2, C3: 16pF; C_0603_1608Metric; digikey 1292-1490-1-ND
C4, C5, C8, C11: 0.1uF; C_0603_1608Metric; digikey 311-1344-1-ND
C6, C9: 10uF; C_0805_2012Metric; digikey 1276-1096-1-ND
C7: 4.7uF; C_0805_2012Metric; digikey 1276-1244-1-ND
D1: LED RED; LED_0603_1608Metric; digikey 3147-B1931URO-20D000114U1930CT-ND
D2: LED GREEN; LED_0603_1608Metric; digikey 3147-B1911PG--20D000514U1930CT-ND
D3: CUS10F30; D_SOD-323; digikey CUS10F30H3FCT-ND
FB1: MH2029-601Y; L_0805_2012Metric; digikey MH2029-601YCT-ND
H1, H2, H3, H4: MP; MountingHole_3.2mm_M3_Pad_Via
J1: USB4105-GF-A; USB_C_5077CR-16-SMC2-BK-TR; digikey 2073-USB4105-GF-ACT-ND
J2: B2B-PH-K-S; JST_PH_B2B-PH-K_1x02_P2.00mm_Vertical; digikey 455-1704-ND
LS1: Speaker_UM1515IA
Q1: SSM3J332R; SOT-23; digikey 4518-SSM3J332RCT-ND
R1, R2, R7: 20K 1%; R_0603_1608Metric; digikey 311-20.0KHRCT-ND
R3: 10K; R_0603_1608Metric; digikey 13-RC0603JR-1010KLCT-ND
R4, R5: 5.1K; R_0603_1608Metric; digikey 311-5.1KGRCT-ND
R6: 2K; R_0603_1608Metric; digikey 311-2.0KGRCT-ND
R8: 12K 1%; R_0603_1608Metric; digikey 311-12.0KCRT-ND
R9, R10: 330; R_0603_1608Metric; digikey 13-RC0603JR-13330RLCT-ND
R11: 100K; R_0603_1608Metric; digikey 311-100KGRCT-ND
R12, R13: 100K/0; R_0603_1608Metric; digikey 311-1.00KHRCT-ND
SW1: PAGE/BOOT; SW_PUSH_6mm_H8mm; digikey 2223-TS02-66-70-BK-160-LCR-D-ND
SW2: ZOOM-IN; SW_PUSH_6mm_H8mm; digikey 2223-TS02-66-70-BK-160-LCR-D-ND
SW3: MODE; SW_PUSH_6mm_H8mm; digikey 2223-TS02-66-70-BK-160-LCR-D-ND
SW4: ZOOM-OUT; SW_PUSH_6mm_H8mm; digikey 2223-TS02-66-70-BK-160-LCR-D-ND
SW5: SLIDE_SW; SLIDE_SW_IS1235-G; digikey SLIDE_SW_IS1235-G https://akizukidenshi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
U1: ESP32-S3-WROOM-1-N16R8; ESP32-S3-WROOM-1_EXP; digikey 1965-ESP32-S3-WROOM-1-N16R8CT-ND
U2: MCP73831T-2ATI/OT; SOT-23-5; digikey MCP73831T-2ATI/OTCT-ND
U3: SPX3819M5-L; SOT-23-5; digikey 1016-1871-1-ND
U4: MAX98357A; TQFN-16-1EP_3x3mm_P0.5mm_EP1.23x1.23mm; digikey MAX98357AETE+TCT-ND
U5: ILI9488 MCU I8080 8/16BIT 3/4; ILI9488 MCU I8080
Y1: 32.7680KHz; Crystal_SMD_3215-2Pin_3.2x1.5mm; digikey 2151-RT3215-32.768-12.5-TRCT-ND

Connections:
+3.3V: C4.1, C8.1, C9.1, C11.1, R3.1, R7.1, R12.2, U1.2 (3V3), U3.5 (OUT), U4.7 (VDD), U4.8 (VDD), U5.1 (VCC)
/GAIN_SLOT: R12.1, R13.1, U4.2 (GAIN_SLOT)
/IO0/BOOT: SW1.2, U1.27 (IO0)
/IO1/TOUCH1: U1.39 (IO1)
/IO2: U1.38 (IO2)
/IO3: U1.15 (IO3), U5.6 (MOSI)
/IO4: U1.4 (IO4), U4.4 (~SD_MODE)
/IO5: U1.5 (IO5), U4.14 (LRCLK)
/IO6: U1.6 (IO6), U4.16 (BCLK)
/IO7: U1.7 (IO7), U4.1 (DIN)
/IO8: U1.12 (IO8), U5.7 (SCK)
/IO9: U1.17 (IO9), U5.4 (RESET)
/IO10: U1.18 (IO10), U5.3 (~CS)
/IO11: R1.2, R2.1, U1.19 (IO11)
/IO12: U1.20 (IO12), U5.15 (SD_CS)
/IO13: U1.21 (IO13), U5.16 (SD_SDI)
/IO14: U1.22 (IO14), U5.17 (SD_SDO)
/IO15/XTAL32KP: C3.1, U1.8 (IO15), Y1.2
/IO16/XTAL32KN: C2.1, U1.9 (IO16), Y1.1
/IO17: U1.10 (IO17), U5.9 (MISO)
/IO18: U1.11 (IO18), U5.8 (BL)
/IO21: U1.23 (IO21), U5.18 (SD_CLK)
/IO38: SW2.2, U1.31 (IO38)
/IO39: SW4.2, U1.32 (IO39)
/IO40: SW3.2, U1.33 (IO40)
/IO41: U1.34 (IO41), U5.13 (TDO)
/IO42: U1.35 (IO42), U5.14 (PEN)
/IO45: U1.26 (IO45), U5.12 (TDI)
/IO46: U1.16 (IO46), U5.5 (D/~C)
/IO47: U1.24 (IO47), U5.10 (TCK)
/IO48: U1.25 (IO48), U5.11 (TCS)
/RXD: U1.36 (RXD0)
/TXD: U1.37 (TXD0)
/USBDM: J1.A7 (D-), J1.B7 (D-), U1.13 (IO19)
/USBDP: J1.A6 (D+), J1.B6 (D+), U1.14 (IO20)
/USBVDD: D3.2 (A), FB1.2, Q1.1, R9.1, R11.1, U2.4 (V_{DD})
/VBAT: C7.1, J2.2, Q1.3, U2.3 (V_{BAT})
/VOUT: C5.1, C6.1, R1.1, SW5.1 (A), U3.1 (IN), U3.3 (EN)
/~RESET: C1.1, R3.2, U1.3 (EN)
GND: C1.2, C2.2, C3.2, C4.2, C5.2, C6.2, C7.2, C8.2, C9.2, C10.2, C11.2, H1.1 (1_1), H2.1 (1_1), H3.1 (1_1), H4.1 (1_1), J1.A1 (GND), J1.A12 (GND), J1.B1 (GND), J1.B12 (GND), J1.S1 (SHIELD), J2.1, R2.2, R4.1, R5.1, R6.2, R8.2, R10.2, R11.2, R13.2, SW1.1, SW2.1, SW3.1, SW4.1, U1.1 (GND), U1.40 (GND), U1.41 (GND), U1.42 (GND), U1.43 (GND), U1.44 (GND), U1.45 (GND), U1.46 (GND), U1.47 (GND), U1.48 (GND), U1.49 (GND), U2.2 (V_{SS}), U3.2 (GND), U4.3 (GND), U4.11 (GND), U4.15 (GND), U4.17 (PAD), U5.2 (GND)
unnamed: D1.2 (A), R9.2
unnamed: D1.1 (K), D2.2 (A), U2.1 (STAT)
unnamed: D2.1 (K), R10.1
unnamed: C10.1, D3.1 (K), Q1.2, SW5.2 (B)
unnamed: FB1.1, J1.A4 (VBUS), J1.A9 (VBUS), J1.B4 (VBUS), J1.B9 (VBUS)
unnamed: J1.A5 (CC1), R5.2
unnamed: J1.B5 (CC2), R4.2
unnamed: R6.1, U2.5 (PROG)
unnamed: R7.2, R8.1, U3.4 (ADJ)
unnamed: LS1.2, U4.10 (OUTN)
unnamed: LS1.1, U4.9 (OUTP)

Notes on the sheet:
R103: 0 Left Channel 210.2K Right Channel 634K Left/2 + Right/2 ASSUMES VGPIO = 3.3v
3dB VCC-100K 6dB VCC-0 9dB OPEN 12dB GND-0 15dB GND-100K DO NOT SHORT VCC-GND

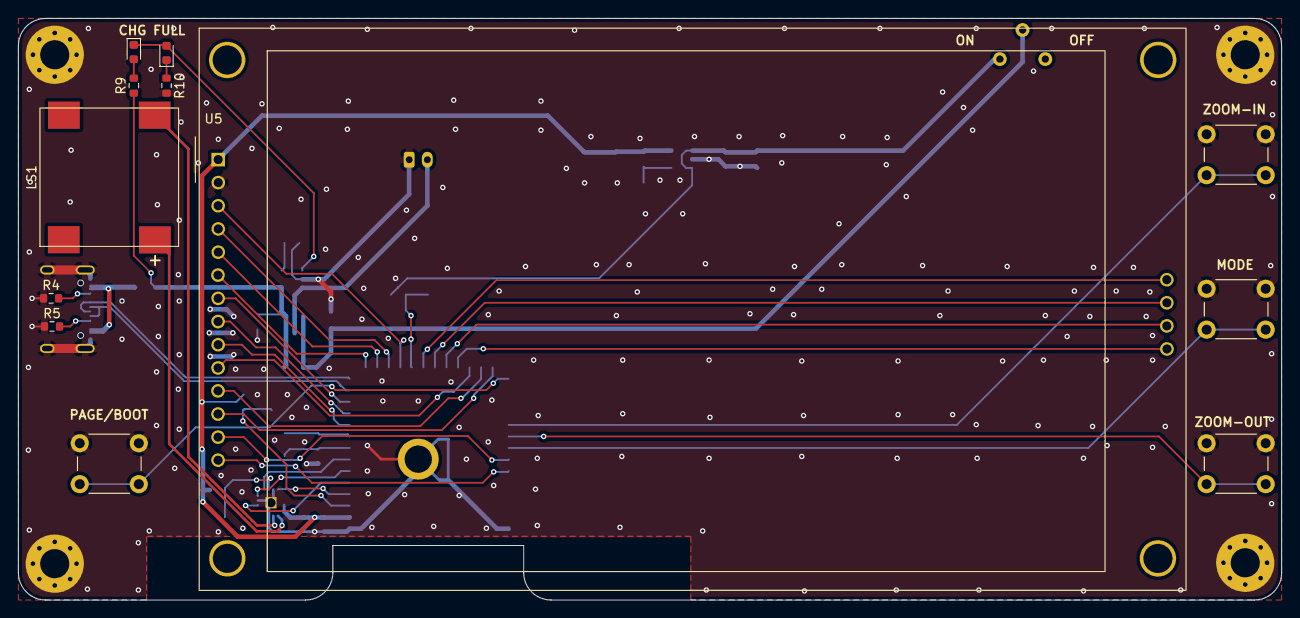
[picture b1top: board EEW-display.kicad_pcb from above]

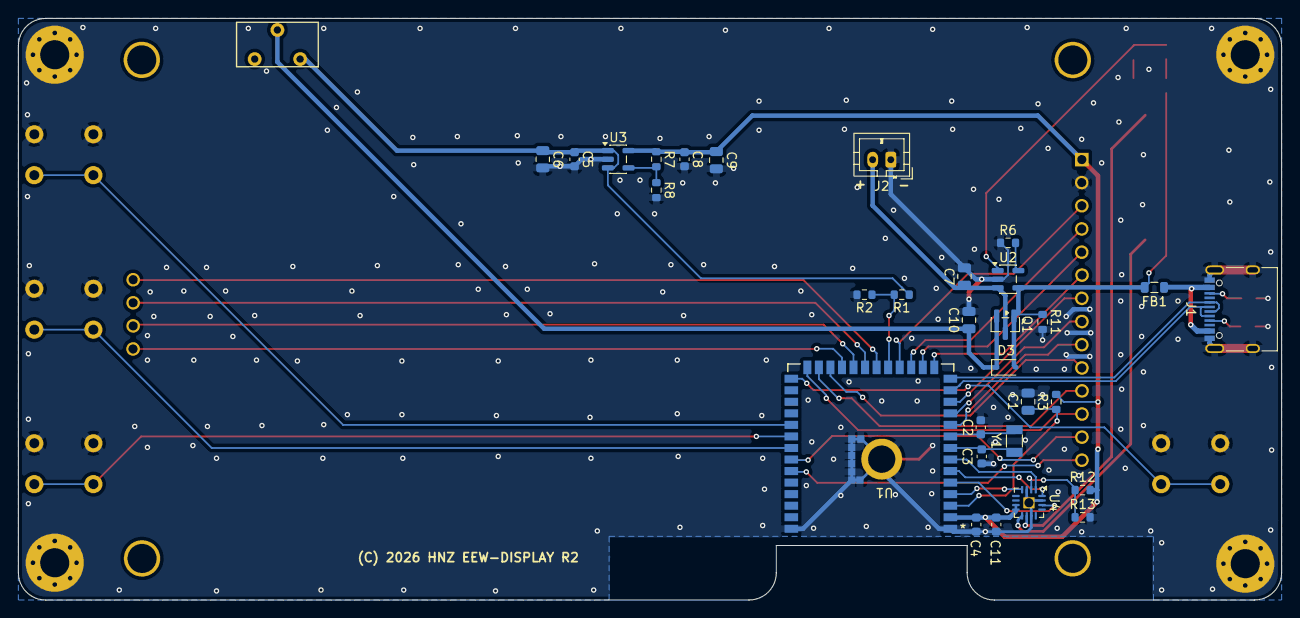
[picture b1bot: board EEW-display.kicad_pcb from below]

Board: 2 copper layers, 139.0 x 64.0 mm, 47 parts (31 on the bottom side), 47 nets.

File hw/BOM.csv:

"Reference","Qty","Value","DNP","Footprint","digikey/other"
"C1,C10","2","1uF","","Capacitor_SMD:C_0805_2012Metric","1276-1026-1-ND"
"C2,C3","2","16pF","","Capacitor_SMD:C_0603_1608Metric","1292-1490-1-ND"
"C4,C5,C8,C11","4","0.1uF","","Capacitor_SMD:C_0603_1608Metric","311-1344-1-ND"
"C6,C9","2","10uF","","Capacitor_SMD:C_0805_2012Metric","1276-1096-1-ND"
"C7","1","4.7uF","","Capacitor_SMD:C_0805_2012Metric","1276-1244-1-ND"
"D1","1","LED RED","","LED_SMD:LED_0603_1608Metric","3147-B1931URO-20D000114U1930CT-ND"
"D2","1","LED GREEN","","LED_SMD:LED_0603_1608Metric","3147-B1911PG--20D000514U1930CT-ND"
"D3","1","CUS10F30","","Diode_SMD:D_SOD-323","CUS10F30H3FCT-ND"
"FB1","1","MH2029-601Y","","Inductor_SMD:L_0805_2012Metric","MH2029-601YCT-ND"
"J1","1","USB4105-GF-A","","Library:USB_C_5077CR-16-SMC2-BK-TR","2073-USB4105-GF-ACT-ND"
"J2","1","B2B-PH-K-S","","Connector_JST:JST_PH_B2B-PH-K_1x02_P2.00mm_Vertical","455-1704-ND"
"LS1","1","Speaker_UM1515IA","","Library:Speaker_UM1515IA","https://akizukidenshi.com/catalog/g/g106707/"
"Q1","1","SSM3J332R","","Package_TO_SOT_SMD:SOT-23","4518-SSM3J332RCT-ND"
"R1,R2,R7","3","20K 1%","","Resistor_SMD:R_0603_1608Metric","311-20.0KHRCT-ND"
"R3","1","10K","","Resistor_SMD:R_0603_1608Metric","13-RC0603JR-1010KLCT-ND"
"R4,R5","2","5.1K","","Resistor_SMD:R_0603_1608Metric","311-5.1KGRCT-ND"
"R6","1","2K","","Resistor_SMD:R_0603_1608Metric","311-2.0KGRCT-ND"
"R8","1","12K 1%","","Resistor_SMD:R_0603_1608Metric","311-12.0KCRT-ND"
"R9,R10","2","330","","Resistor_SMD:R_0603_1608Metric","13-RC0603JR-13330RLCT-ND"
"R11","1","100K","","Resistor_SMD:R_0603_1608Metric","311-100KGRCT-ND"
"R12,R13","2","100K/0","","Resistor_SMD:R_0603_1608Metric","311-1.00KHRCT-ND"
"SW1","1","PAGE/BOOT","","Button_Switch_THT:SW_PUSH_6mm_H8mm","2223-TS02-66-70-BK-160-LCR-D-ND"
"SW2","1","ZOOM-IN","","Button_Switch_THT:SW_PUSH_6mm_H8mm","2223-TS02-66-70-BK-160-LCR-D-ND"
"SW3","1","MODE","","Button_Switch_THT:SW_PUSH_6mm_H8mm","2223-TS02-66-70-BK-160-LCR-D-ND"
"SW4","1","ZOOM-OUT","","Button_Switch_THT:SW_PUSH_6mm_H8mm","2223-TS02-66-70-BK-160-LCR-D-ND"
"SW5","1","SLIDE_SW","","Library:SLIDE_SW_IS1235-G","SLIDE_SW_IS1235-G  https://akizukidenshi.com/catalog/g/g115368/"
"U1","1","ESP32-S3-WROOM-1-N16R8","","Library:ESP32-S3-WROOM-1_EXP","1965-ESP32-S3-WROOM-1-N16R8CT-ND"
"U2","1","MCP73831T-2ATI/OT","","Package_TO_SOT_SMD:SOT-23-5","MCP73831T-2ATI/OTCT-ND"
"U3","1","SPX3819M5-L","","Package_TO_SOT_SMD:SOT-23-5","1016-1871-1-ND"
"U4","1","MAX98357A","","Library:TQFN-16-1EP_3x3mm_P0.5mm_EP1.23x1.23mm","MAX98357AETE+TCT-ND"
"U5","1","ILI9488 MCU I8080 8/16BIT 3/4","","Library:ILI9488 MCU I8080","-"
"Y1","1","32.7680KHz","","Crystal:Crystal_SMD_3215-2Pin_3.2x1.5mm","2151-RT3215-32.768-12.5-TRCT-ND"

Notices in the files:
hw/EEW-display.kicad_pcb:
(C) 2026 HNZ EEW-DISPLAY R2
hw/EEW-display.kicad_sch:
Licensed under CC-BY-SA V4.0
(C) 2026 Hiroshi Nakajima
